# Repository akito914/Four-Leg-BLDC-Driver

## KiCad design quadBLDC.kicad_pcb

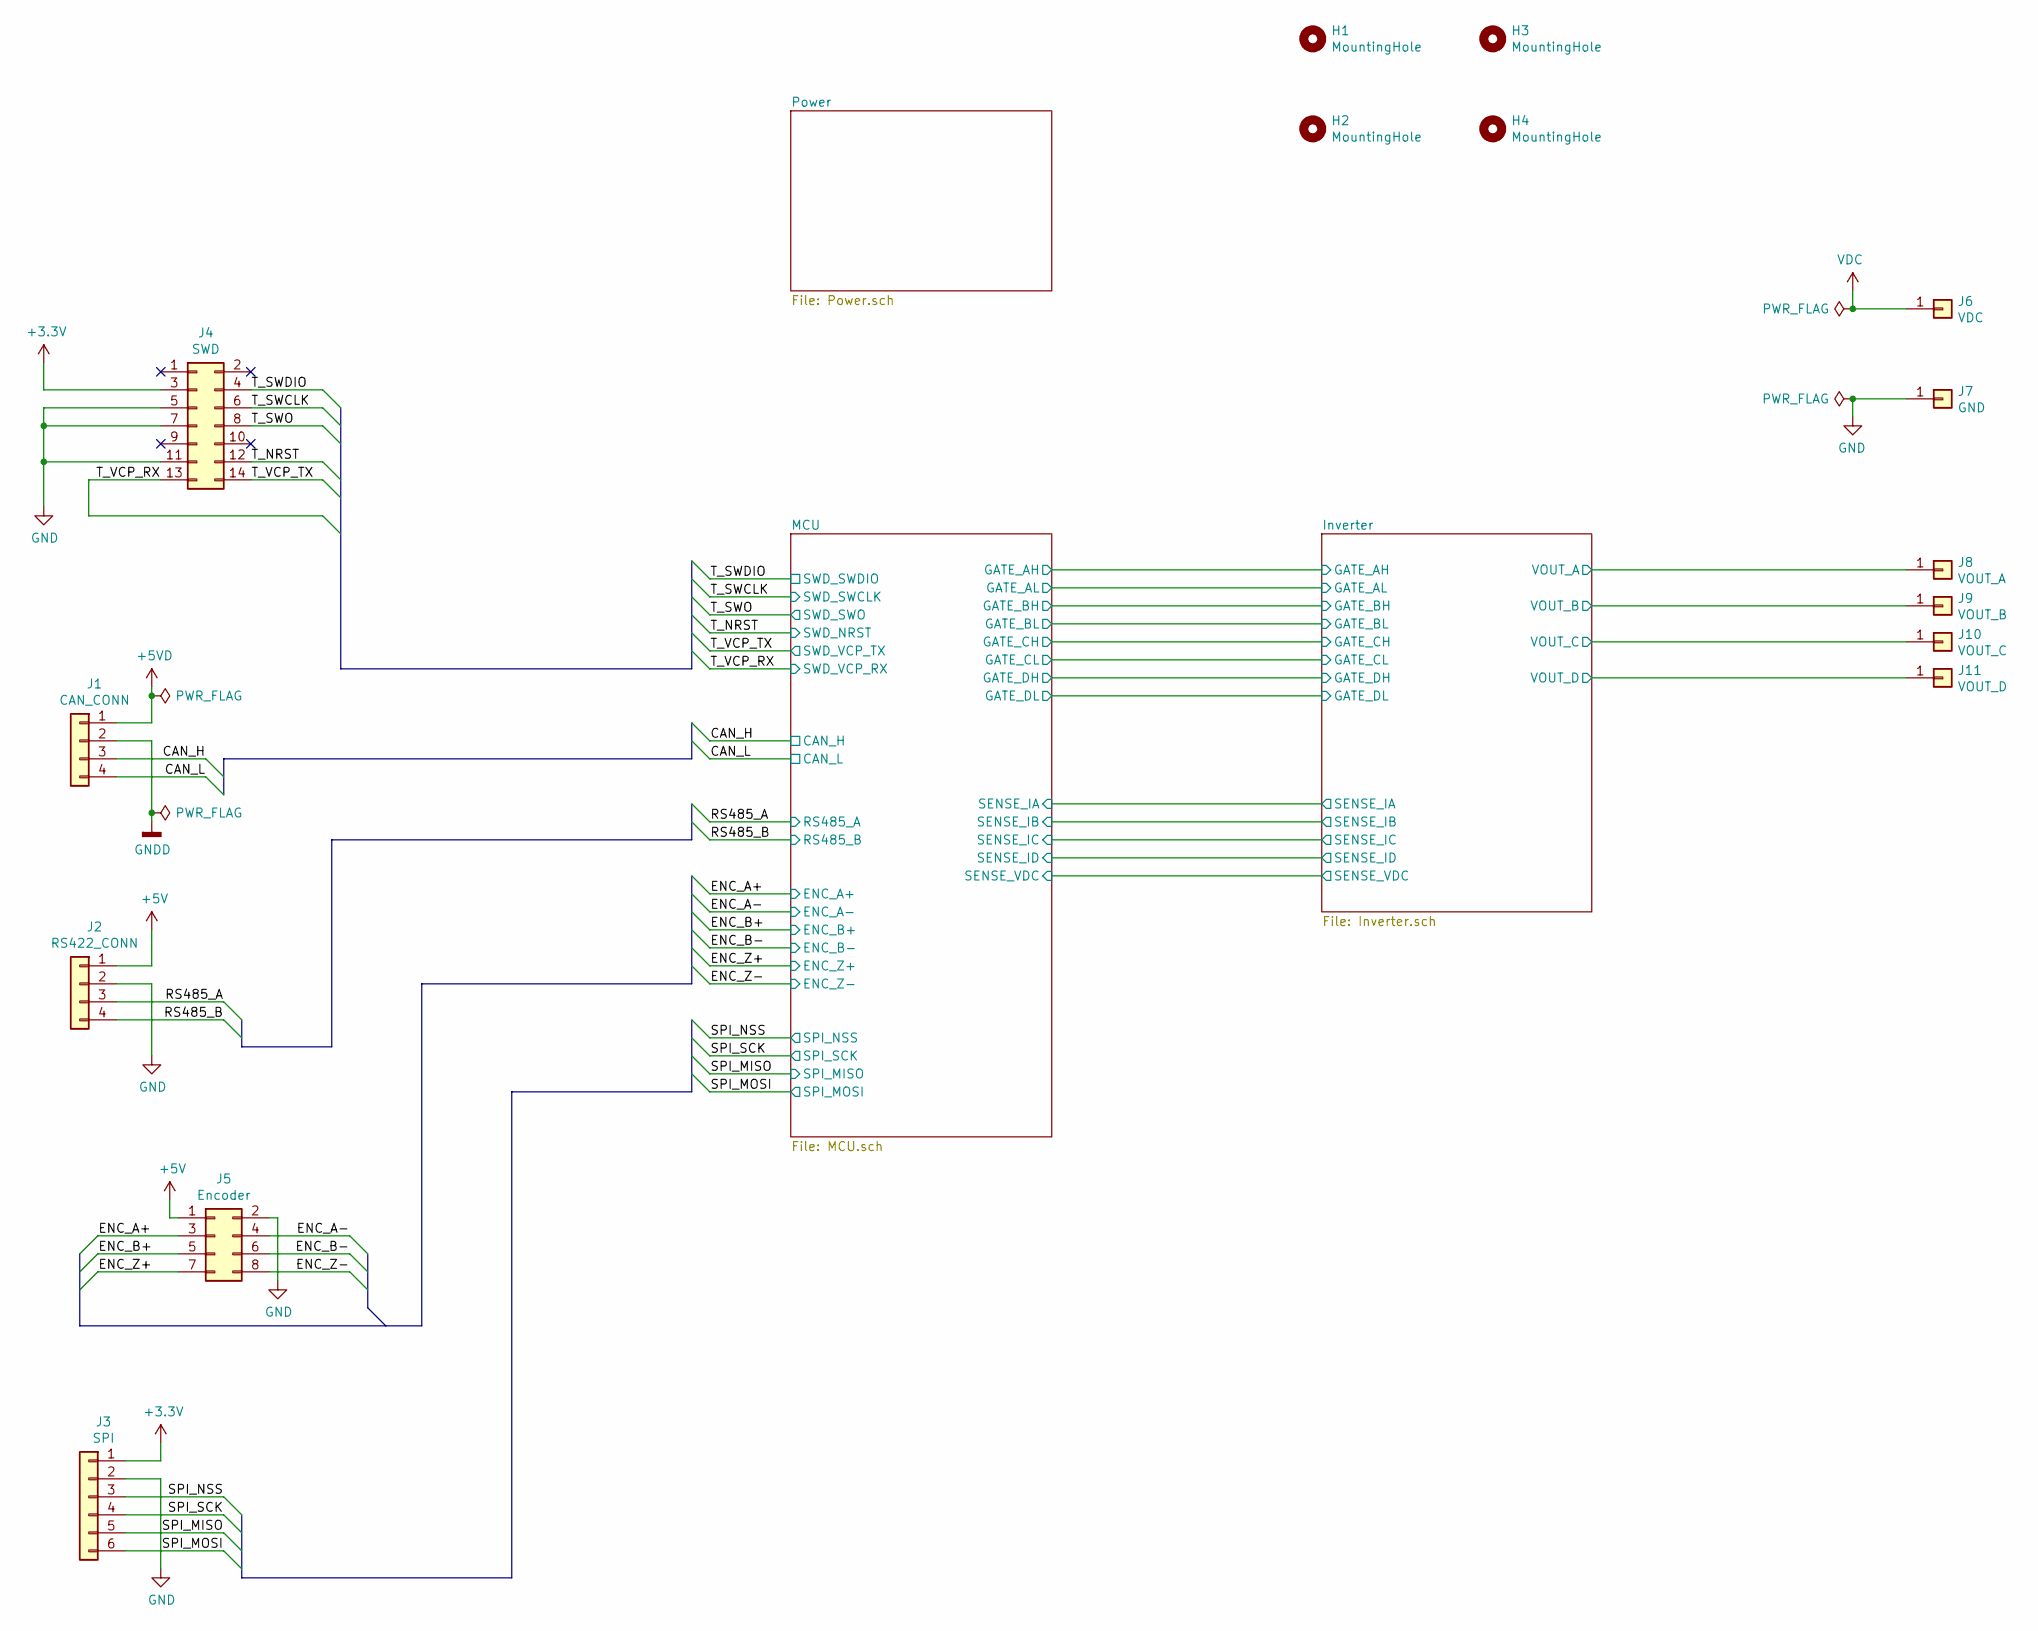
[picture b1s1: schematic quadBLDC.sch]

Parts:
H1, H2, H3, H4: MountingHole; MountingHole_3.2mm_M3
J1: CAN_CONN; JST_PH_B4B-PH-K_1x04_P2.00mm_Vertical
J2: RS422_CONN; JST_PH_B4B-PH-K_1x04_P2.00mm_Vertical
J3: SPI; JST_PH_B6B-PH-K_1x06_P2.00mm_Vertical
J4: SWD; PinHeader_2x07_P1.27mm_Vertical_SMD
J5: Encoder; JST_PHD_B8B-PHDSS_2x04_P2.00mm_Vertical
J6: VDC; SolderWire-2.5sqmm_1x01_D2.4mm_OD3.6mm
J7: GND; SolderWire-2.5sqmm_1x01_D2.4mm_OD3.6mm
J8: VOUT_A; SolderWire-2.5sqmm_1x01_D2.4mm_OD3.6mm
J9: VOUT_B; SolderWire-2.5sqmm_1x01_D2.4mm_OD3.6mm
J10: VOUT_C; SolderWire-2.5sqmm_1x01_D2.4mm_OD3.6mm
J11: VOUT_D; SolderWire-2.5sqmm_1x01_D2.4mm_OD3.6mm

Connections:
+3V3: J3.1, J4.3; also elsewhere on the board
+5V: J2.1, J5.1; also elsewhere on the board
+5VD: J1.1; also elsewhere on the board
/CAN_H: J1.3; also elsewhere on the board
/CAN_L: J1.4; also elsewhere on the board
/ENC_A+: J5.3; also elsewhere on the board
/ENC_A-: J5.4; also elsewhere on the board
/ENC_B+: J5.5; also elsewhere on the board
/ENC_B-: J5.6; also elsewhere on the board
/ENC_Z+: J5.7; also elsewhere on the board
/ENC_Z-: J5.8; also elsewhere on the board
/Inverter/VOUT_A: J8.1; also elsewhere on the board
/Inverter/VOUT_B: J9.1; also elsewhere on the board
/Inverter/VOUT_C: J10.1; also elsewhere on the board
/Inverter/VOUT_D: J11.1; also elsewhere on the board
/RS485_A: J2.3; also elsewhere on the board
/RS485_B: J2.4; also elsewhere on the board
/SPI_MISO: J3.5; also elsewhere on the board
/SPI_MOSI: J3.6; also elsewhere on the board
/SPI_NSS: J3.3; also elsewhere on the board
/SPI_SCK: J3.4; also elsewhere on the board
/T_NRST: J4.12; also elsewhere on the board
/T_SWCLK: J4.6; also elsewhere on the board
/T_SWDIO: J4.4; also elsewhere on the board
/T_SWO: J4.8; also elsewhere on the board
/T_VCP_RX: J4.13; also elsewhere on the board
/T_VCP_TX: J4.14; also elsewhere on the board
GND: J2.2, J3.2, J4.5, J4.7, J4.11, J5.2, J7.1; also elsewhere on the board
GNDD: J1.2; also elsewhere on the board
VDC: J6.1; also elsewhere on the board

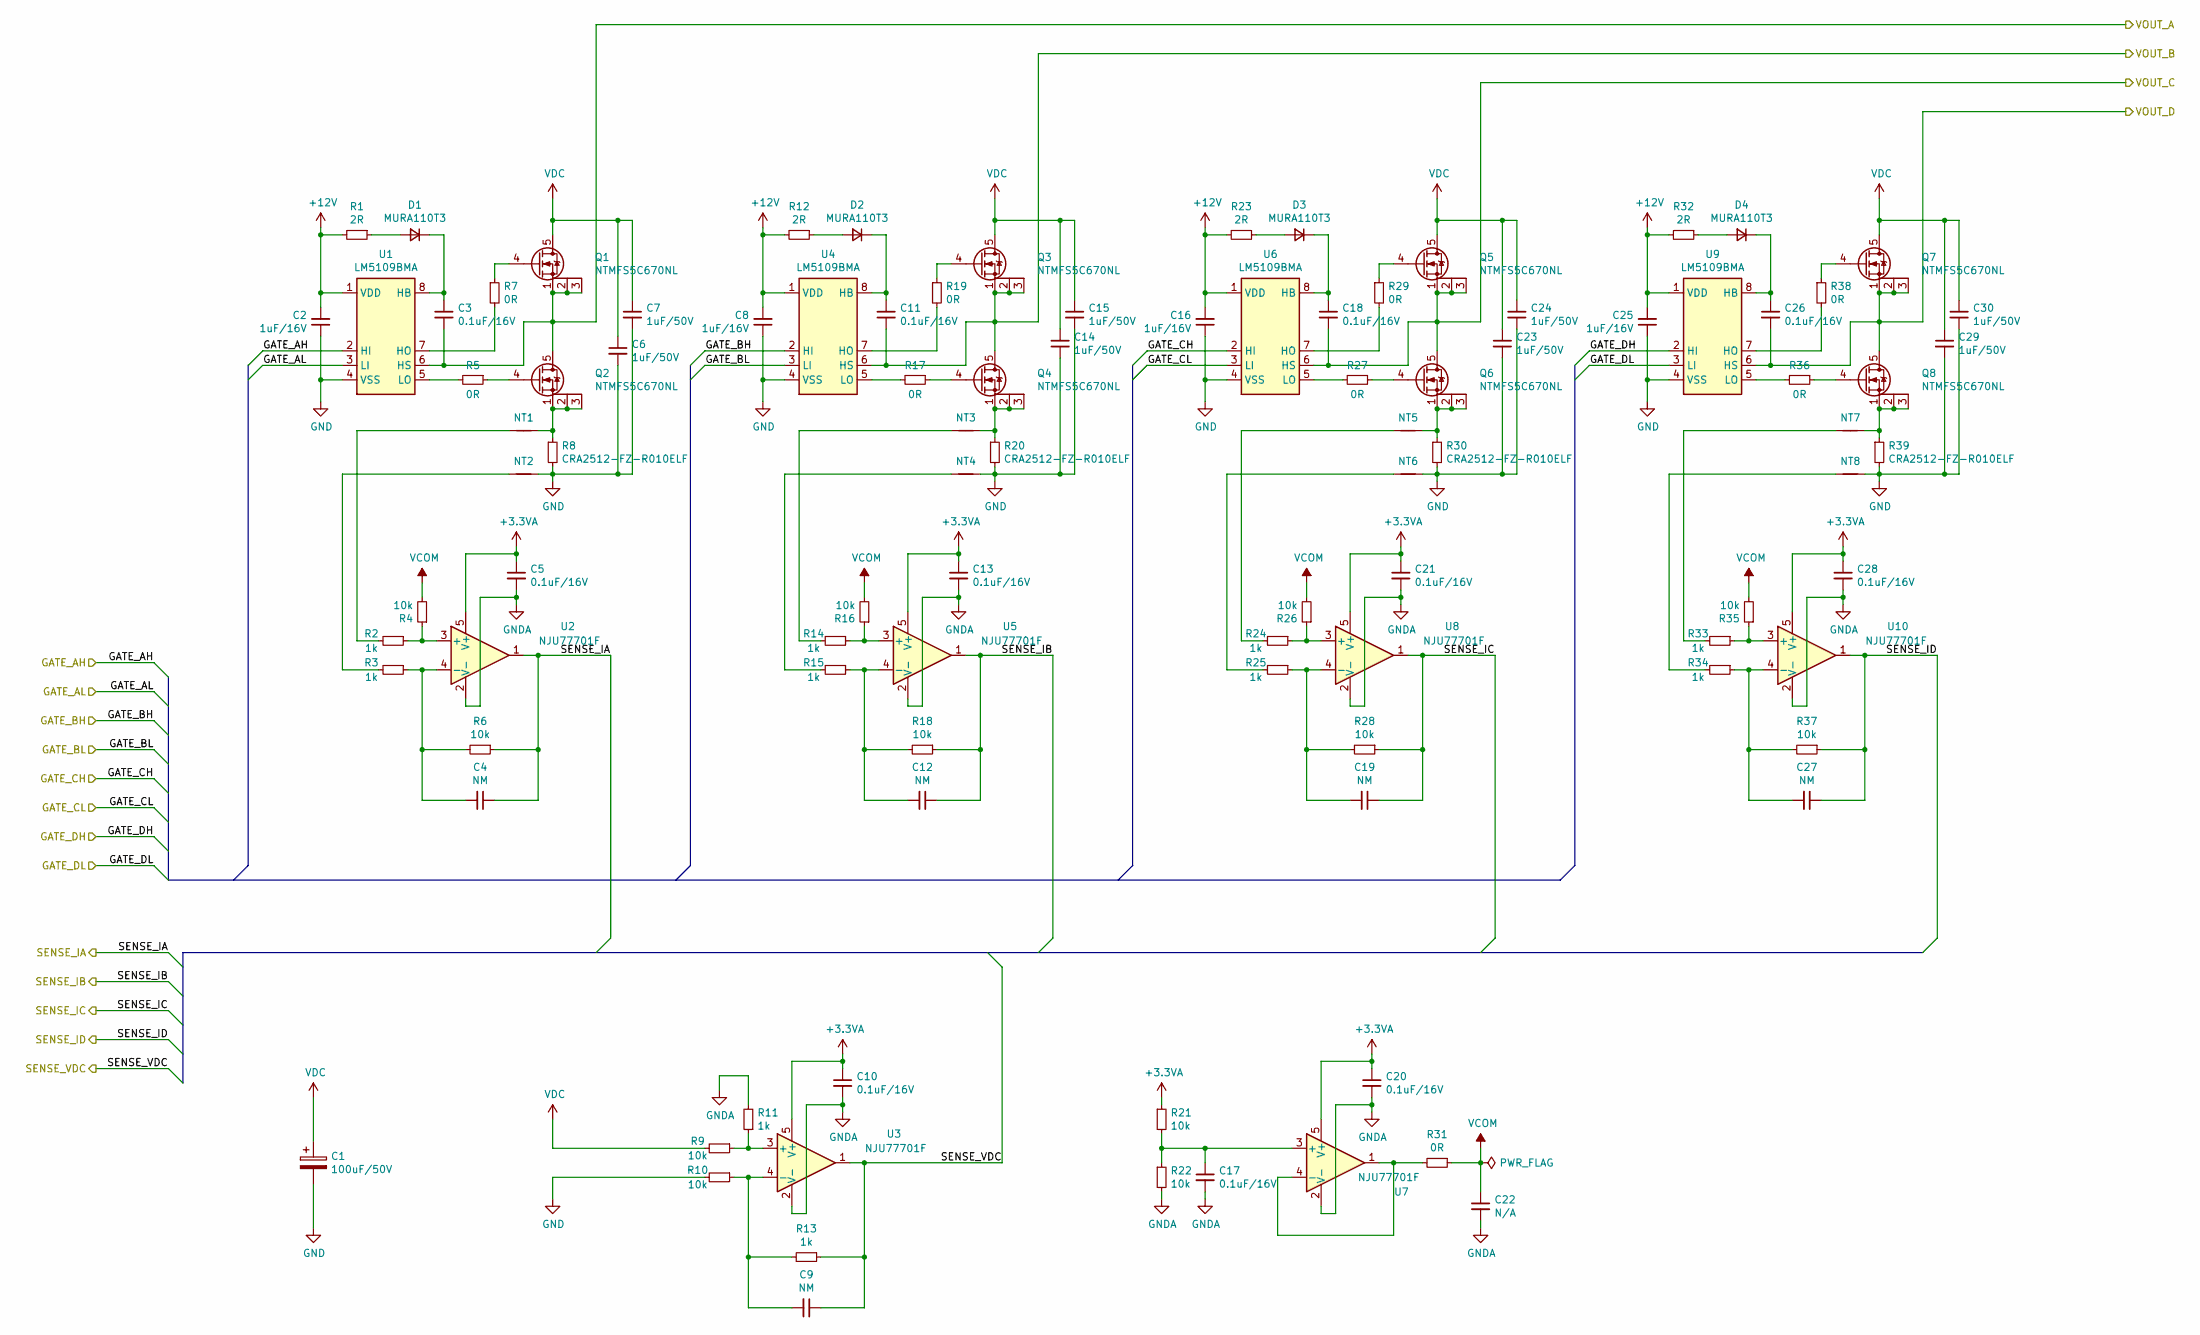
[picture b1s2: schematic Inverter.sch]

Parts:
C1: 100uF/50V; CP_Elec_10x10
C2, C8, C16, C25: 1uF/16V; C_0603_1608Metric
C3, C5, C10, C11, C13, C17, C18, C20, C21, C26, C28: 0.1uF/16V; C_0603_1608Metric
C4, C9, C12, C19, C27: NM; C_0603_1608Metric
C6, C7, C14, C15, C23, C24, C29, C30: 1uF/50V; C_0805_2012Metric
C22: N/A; C_0603_1608Metric
D1, D2, D3, D4: MURA110T3; D_SMA
NT1, NT2, NT3, NT4, NT5, NT6, NT7, NT8: Net-Tie_2; NetTie-2_SMD_Pad0.5mm
Q1, Q2, Q3, Q4, Q5, Q6, Q7, Q8: NTMFS5C670NL; PowerPAK_SO-8_Single
R1, R12, R23, R32: 2R; R_0603_1608Metric
R2, R3, R11, R13, R14, R15, R24, R25, R33, R34: 1k; R_0603_1608Metric
R4, R6, R9, R10, R16, R18, R21, R22, R26, R28, R35, R37: 10k; R_0603_1608Metric
R5, R7, R17, R19, R27, R29, R31, R36, R38: 0R; R_0603_1608Metric
R8, R20, R30, R39: CRA2512-FZ-R010ELF; R_2512_6332Metric
U1, U4, U6, U9: LM5109BMA; SOIC-8_3.9x4.9mm_P1.27mm
U2, U3, U5, U7, U8, U10: NJU77701F; SOT-23-5

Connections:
+3.3VA: C5.1, C10.1, C13.1, C20.1, C21.1, C28.1, R21.1, U2.5 (V+), U3.5 (V+), U5.5 (V+), U7.5 (V+), U8.5 (V+), U10.5 (V+); also elsewhere on the board
+12V: C2.2, C8.2, C16.2, C25.2, R1.2, R12.2, R23.2, R32.2, U1.1 (VDD), U4.1 (VDD), U6.1 (VDD), U9.1 (VDD); also elsewhere on the board
/Inverter/GATE_AH: U1.2 (HI); also elsewhere on the board
/Inverter/GATE_AL: U1.3 (LI); also elsewhere on the board
/Inverter/GATE_BH: U4.2 (HI); also elsewhere on the board
/Inverter/GATE_BL: U4.3 (LI); also elsewhere on the board
/Inverter/GATE_CH: U6.2 (HI); also elsewhere on the board
/Inverter/GATE_CL: U6.3 (LI); also elsewhere on the board
/Inverter/GATE_DH: U9.2 (HI); also elsewhere on the board
/Inverter/GATE_DL: U9.3 (LI); also elsewhere on the board
/Inverter/SENSE_IA: C4.1, R6.1, U2.1; also elsewhere on the board
/Inverter/SENSE_IB: C12.1, R18.1, U5.1; also elsewhere on the board
/Inverter/SENSE_IC: C19.1, R28.1, U8.1; also elsewhere on the board
/Inverter/SENSE_ID: C27.1, R37.1, U10.1; also elsewhere on the board
/Inverter/SENSE_VDC: C9.1, R13.1, U3.1; also elsewhere on the board
/Inverter/VOUT_A: C3.2, Q1.1 (S), Q1.2 (D), Q1.3 (D), Q2.5 (D), U1.6 (HS); also elsewhere on the board
/Inverter/VOUT_B: C11.2, Q3.1 (S), Q3.2 (D), Q3.3 (D), Q4.5 (D), U4.6 (HS); also elsewhere on the board
/Inverter/VOUT_C: C18.2, Q5.1 (S), Q5.2 (D), Q5.3 (D), Q6.5 (D), U6.6 (HS); also elsewhere on the board
/Inverter/VOUT_D: C26.2, Q7.1 (S), Q7.2 (D), Q7.3 (D), Q8.5 (D), U9.6 (HS); also elsewhere on the board
GND: C1.2, C2.1, C6.2, C7.2, C8.1, C14.2, C15.2, C16.1, C23.2, C24.2, C25.1, C29.2, C30.2, NT2.1, NT4.1, NT6.1, NT8.1, R8.2, R10.2, R20.2, R30.2, R39.2, U1.4 (VSS), U4.4 (VSS), U6.4 (VSS), U9.4 (VSS); also elsewhere on the board
GNDA: C5.2, C10.2, C13.2, C17.2, C20.2, C21.2, C22.2, C28.2, R11.2, R22.2, U2.2 (V-), U3.2 (V-), U5.2 (V-), U7.2 (V-), U8.2 (V-), U10.2 (V-); also elsewhere on the board
unnamed: C3.1, D1.1 (K), U1.8 (HB)
unnamed: C4.2, R3.1, R6.2, U2.4 (-)
unnamed: C9.2, R10.1, R13.2, U3.4 (-)
unnamed: C11.1, D2.1 (K), U4.8 (HB)
unnamed: C12.2, R15.1, R18.2, U5.4 (-)
unnamed: C17.1, R21.2, R22.1, U7.3 (+)
unnamed: C18.1, D3.1 (K), U6.8 (HB)
unnamed: C19.2, R25.1, R28.2, U8.4 (-)
unnamed: C26.1, D4.1 (K), U9.8 (HB)
unnamed: C27.2, R34.1, R37.2, U10.4 (-)
unnamed: D1.2 (A), R1.1
unnamed: D2.2 (A), R12.1
unnamed: D3.2 (A), R23.1
unnamed: D4.2 (A), R32.1
unnamed: NT1.1, Q2.1 (S), Q2.2 (D), Q2.3 (D), R8.1
unnamed: NT1.2, R2.2
unnamed: NT2.2, R3.2
unnamed: NT3.1, Q4.1 (S), Q4.2 (D), Q4.3 (D), R20.1
unnamed: NT3.2, R14.2
unnamed: NT4.2, R15.2
unnamed: NT5.1, Q6.1 (S), Q6.2 (D), Q6.3 (D), R30.1
unnamed: NT5.2, R24.2
unnamed: NT6.2, R25.2
unnamed: NT7.1, Q8.1 (S), Q8.2 (D), Q8.3 (D), R39.1
unnamed: NT7.2, R33.2
unnamed: NT8.2, R34.2
unnamed: Q1.4 (G), R7.1
unnamed: Q2.4 (G), R5.1
unnamed: Q3.4 (G), R19.1
unnamed: Q4.4 (G), R17.1
unnamed: Q5.4 (G), R29.1
unnamed: Q6.4 (G), R27.1
unnamed: Q7.4 (G), R38.1
unnamed: Q8.4 (G), R36.1
unnamed: R2.1, R4.1, U2.3 (+)
unnamed: R5.2, U1.5 (LO)
unnamed: R7.2, U1.7 (HO)
unnamed: R9.1, R11.1, U3.3 (+)
unnamed: R14.1, R16.1, U5.3 (+)
unnamed: R17.2, U4.5 (LO)
unnamed: R19.2, U4.7 (HO)
unnamed: R24.1, R26.1, U8.3 (+)
unnamed: R27.2, U6.5 (LO)
unnamed: R29.2, U6.7 (HO)
unnamed: R31.2, U7.1, U7.4 (-)
unnamed: R33.1, R35.1, U10.3 (+)
unnamed: R36.2, U9.5 (LO)
unnamed: R38.2, U9.7 (HO)
VCOM: C22.1, R4.2, R16.2, R26.2, R31.1, R35.2
VDC: C1.1, C6.1, C7.1, C14.1, C15.1, C23.1, C24.1, C29.1, C30.1, Q1.5 (D), Q3.5 (D), Q5.5 (D), Q7.5 (D), R9.2; also elsewhere on the board

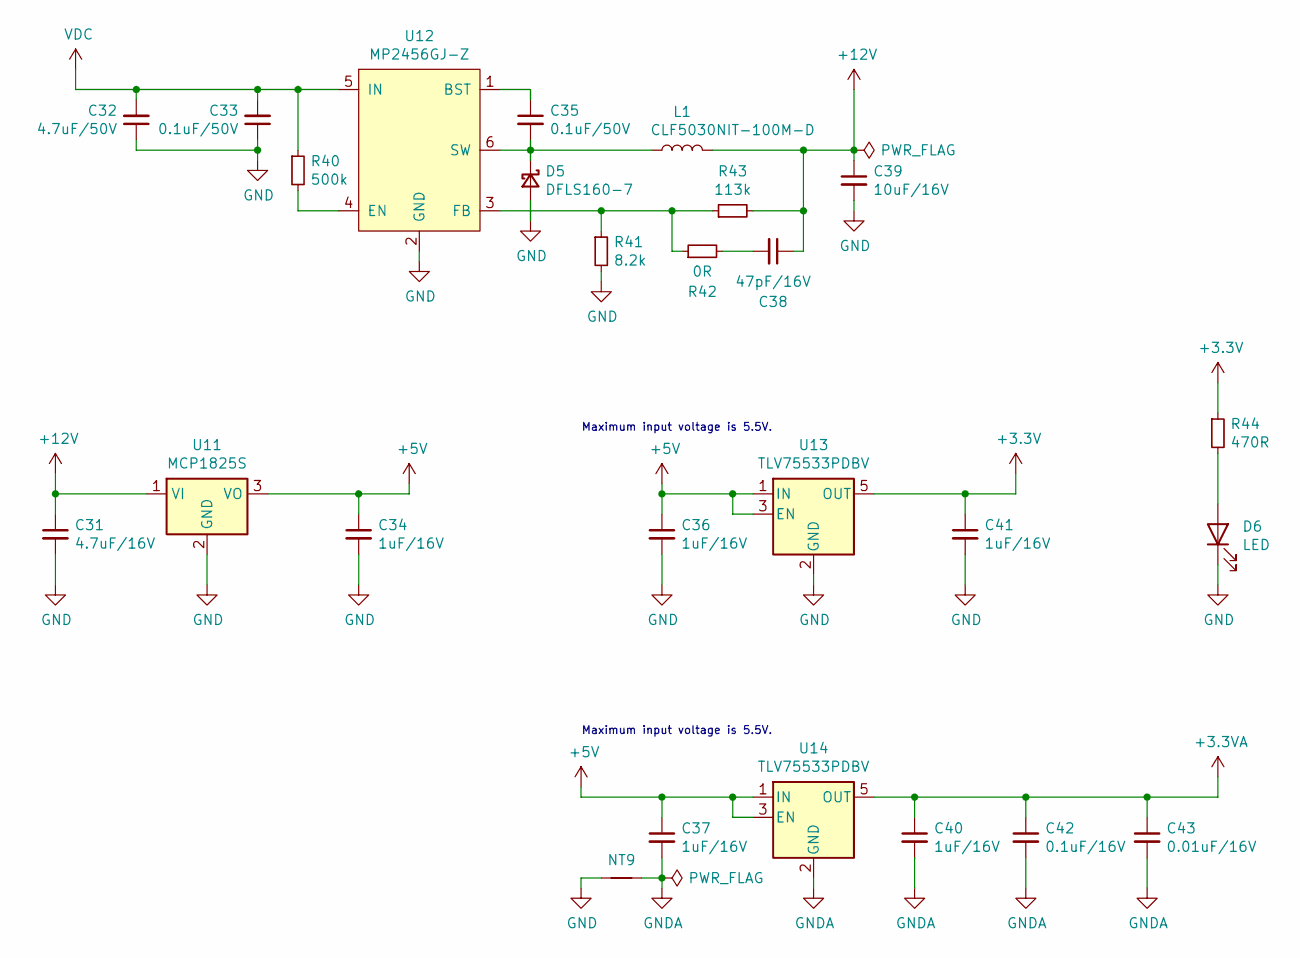
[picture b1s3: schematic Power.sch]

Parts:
C31: 4.7uF/16V; C_0805_2012Metric
C32: 4.7uF/50V; C_0805_2012Metric
C33, C35: 0.1uF/50V; C_0603_1608Metric
C34, C36, C37, C40, C41: 1uF/16V; C_0603_1608Metric
C38: 47pF/16V; C_0603_1608Metric
C39: 10uF/16V; C_0805_2012Metric
C42: 0.1uF/16V; C_0603_1608Metric
C43: 0.01uF/16V; C_0603_1608Metric
D5: DFLS160-7; D_PowerDI-123
D6: LED; LED_0603_1608Metric
L1: CLF5030NIT-100M-D; L_TDK_CLF5030NI-D
NT9: Net-Tie_2; NetTie-2_SMD_Pad0.5mm
R40: 500k; R_0603_1608Metric
R41: 8.2k; R_0603_1608Metric
R42: 0R; R_0603_1608Metric
R43: 113k; R_0603_1608Metric
R44: 470R; R_0603_1608Metric
U11: MCP1825S; SOT-223-3_TabPin2
U12: MP2456GJ-Z; SOT-23-6
U13, U14: TLV75533PDBV; SOT-23-5

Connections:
+3.3VA: C40.1, C42.1, C43.1, U14.5 (OUT); also elsewhere on the board
+3V3: C41.1, R44.1, U13.5 (OUT); also elsewhere on the board
+5V: C34.1, C36.1, C37.1, U11.3 (VO), U13.1 (IN), U13.3 (EN), U14.1 (IN), U14.3 (EN); also elsewhere on the board
+12V: C31.1, C38.1, C39.1, L1.2, R43.2, U11.1 (VI); also elsewhere on the board
GND: C31.2, C32.1, C33.1, C34.2, C36.2, C39.2, C41.2, D5.2 (A), D6.1 (K), NT9.2, R41.2, U11.2 (GND), U12.2 (GND), U13.2 (GND); also elsewhere on the board
GNDA: C37.2, C40.2, C42.2, C43.2, NT9.1, U14.2 (GND); also elsewhere on the board
unnamed: C35.1, U12.1 (BST)
unnamed: C35.2, D5.1 (K), L1.1, U12.6 (SW)
unnamed: C38.2, R42.2
unnamed: D6.2 (A), R44.2
unnamed: R40.2, U12.4 (EN)
unnamed: R41.1, R42.1, R43.1, U12.3 (FB)
VDC: C32.2, C33.2, R40.1, U12.5 (IN); also elsewhere on the board

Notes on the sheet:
Maximum input voltage is 5.5V.

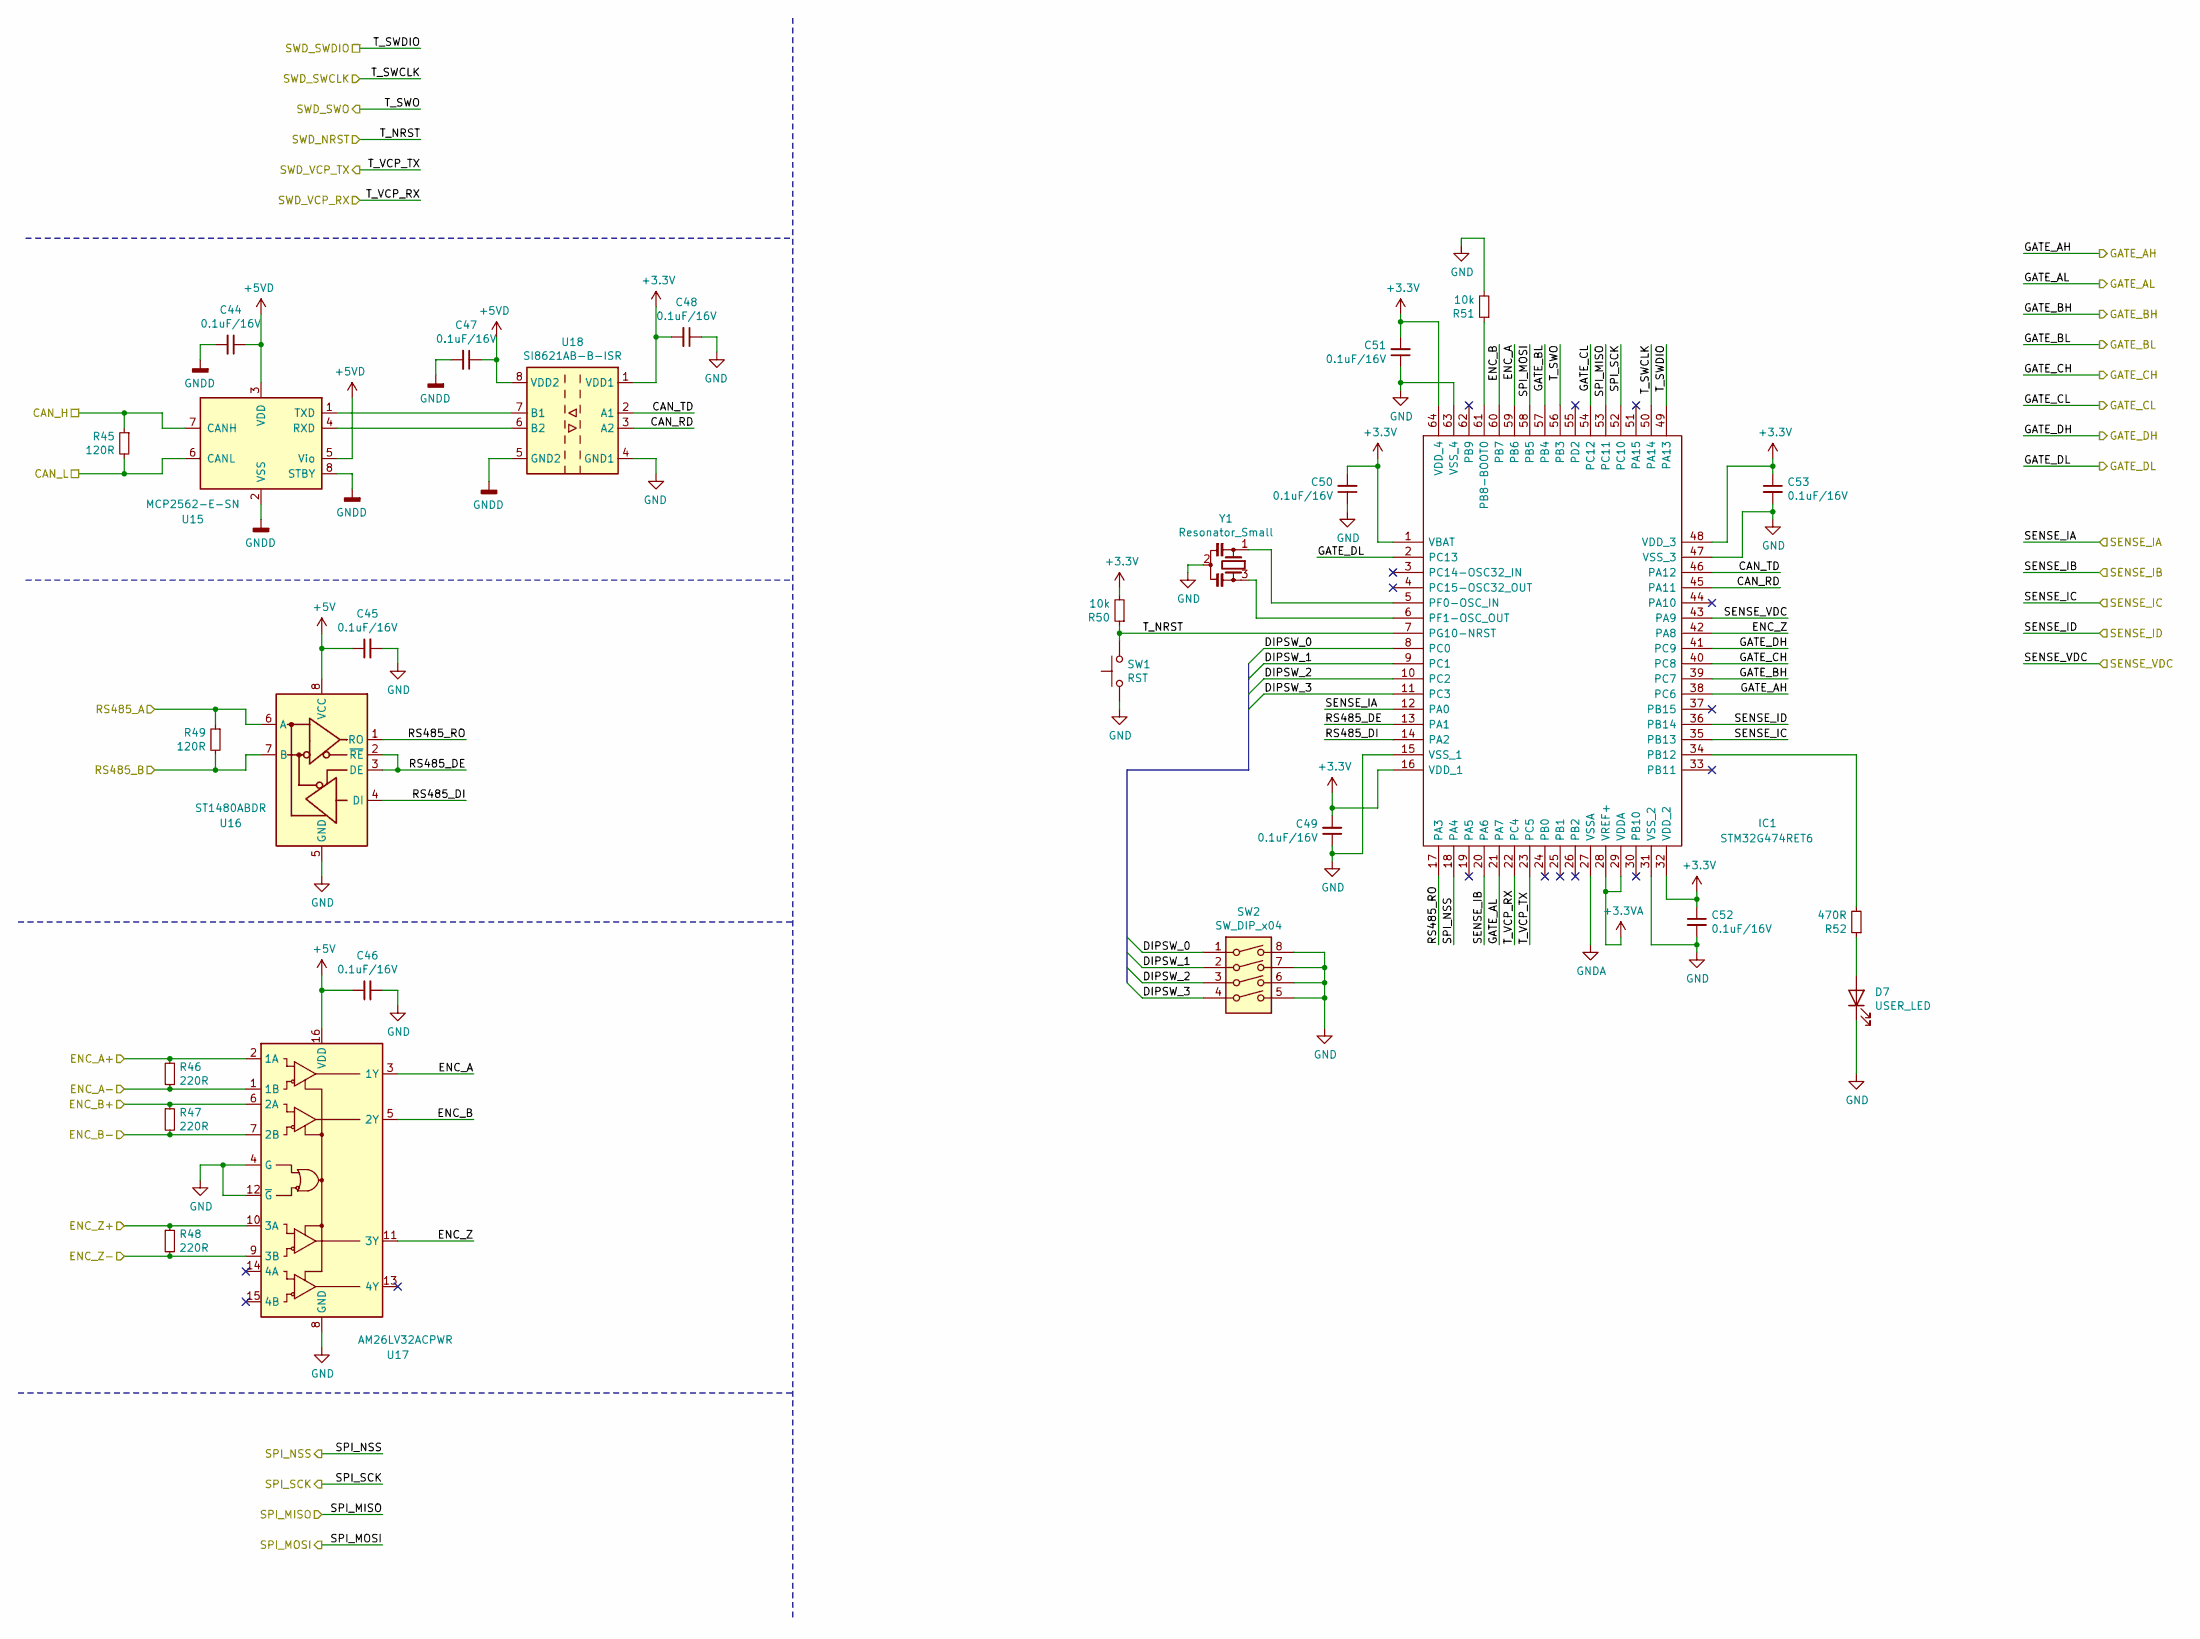
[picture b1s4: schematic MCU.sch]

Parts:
C44, C45, C46, C47, C48, C49, C50, C51, C52, C53: 0.1uF/16V; C_0603_1608Metric
D7: USER_LED; LED_0603_1608Metric
IC1: STM32G474RET6; QFP50P1200X1200X160-64N
R45, R49: 120R; R_0603_1608Metric
R46, R47, R48: 220R; R_0603_1608Metric
R50, R51: 10k; R_0603_1608Metric
R52: 470R; R_0603_1608Metric
SW1: RST; SKRPACE010
SW2: SW_DIP_x04; SOIC127P812X230-8N
U15: MCP2562-E-SN; SOIC-8_3.9x4.9mm_P1.27mm
U16: ST1480ABDR; SOIC-8_3.9x4.9mm_P1.27mm
U17: AM26LV32ACPWR; TSSOP-16_4.4x5mm_P0.65mm
U18: SI8621AB-B-ISR; SOIC-8_3.9x4.9mm_P1.27mm
Y1: Resonator_Small; Resonator_SMD_muRata_CSTxExxV-3Pin_3.0x1.1mm

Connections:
+3.3VA: IC1.28 (VREF+), IC1.29 (VDDA); also elsewhere on the board
+3V3: C48.2, C49.2, C50.2, C51.2, C52.1, C53.1, IC1.1 (VBAT), IC1.16 (VDD_1), IC1.32 (VDD_2), IC1.48 (VDD_3), IC1.64 (VDD_4), R50.2, U18.1 (VDD1); also elsewhere on the board
+5V: C45.1, C46.1, U16.8 (VCC), U17.16 (VDD); also elsewhere on the board
+5VD: C44.1, C47.1, U15.3 (VDD), U15.5 (Vio), U18.8 (VDD2); also elsewhere on the board
/CAN_H: R45.1, U15.7 (CANH); also elsewhere on the board
/CAN_L: R45.2, U15.6 (CANL); also elsewhere on the board
/ENC_A+: R46.1, U17.2 (1A); also elsewhere on the board
/ENC_A-: R46.2, U17.1 (1B); also elsewhere on the board
/ENC_B+: R47.1, U17.6 (2A); also elsewhere on the board
/ENC_B-: R47.2, U17.7 (2B); also elsewhere on the board
/ENC_Z+: R48.1, U17.10 (3A); also elsewhere on the board
/ENC_Z-: R48.2, U17.9 (3B); also elsewhere on the board
/Inverter/GATE_AH: IC1.38 (PC6); also elsewhere on the board
/Inverter/GATE_AL: IC1.21 (PA7); also elsewhere on the board
/Inverter/GATE_BH: IC1.39 (PC7); also elsewhere on the board
/Inverter/GATE_BL: IC1.57 (PB4); also elsewhere on the board
/Inverter/GATE_CH: IC1.40 (PC8); also elsewhere on the board
/Inverter/GATE_CL: IC1.54 (PC12); also elsewhere on the board
/Inverter/GATE_DH: IC1.41 (PC9); also elsewhere on the board
/Inverter/GATE_DL: IC1.2 (PC13); also elsewhere on the board
/Inverter/SENSE_IA: IC1.12 (PA0); also elsewhere on the board
/Inverter/SENSE_IB: IC1.20 (PA6); also elsewhere on the board
/Inverter/SENSE_IC: IC1.35 (PB13); also elsewhere on the board
/Inverter/SENSE_ID: IC1.36 (PB14); also elsewhere on the board
/Inverter/SENSE_VDC: IC1.43 (PA9); also elsewhere on the board
/MCU/CAN_RD: IC1.45 (PA11), U18.3 (A2)
/MCU/CAN_TD: IC1.46 (PA12), U18.2 (A1)
/MCU/DIPSW_0: IC1.8 (PC0), SW2.1
/MCU/DIPSW_1: IC1.9 (PC1), SW2.2
/MCU/DIPSW_2: IC1.10 (PC2), SW2.3
/MCU/DIPSW_3: IC1.11 (PC3), SW2.4
/MCU/ENC_A: IC1.59 (PB6), U17.3 (1Y)
/MCU/ENC_B: IC1.60 (PB7), U17.5 (2Y)
/MCU/ENC_Z: IC1.42 (PA8), U17.11 (3Y)
/MCU/RS485_DE: IC1.13 (PA1), U16.2 (~RE), U16.3 (DE)
/MCU/RS485_DI: IC1.14 (PA2), U16.4 (DI)
/MCU/RS485_RO: IC1.17 (PA3), U16.1 (RO)
/RS485_A: R49.1, U16.6 (A); also elsewhere on the board
/RS485_B: R49.2, U16.7 (B); also elsewhere on the board
/SPI_MISO: IC1.53 (PC11); also elsewhere on the board
/SPI_MOSI: IC1.58 (PB5); also elsewhere on the board
/SPI_NSS: IC1.18 (PA4); also elsewhere on the board
/SPI_SCK: IC1.52 (PC10); also elsewhere on the board
/T_NRST: IC1.7 (PG10-NRST), R50.1, SW1.2; also elsewhere on the board
/T_SWCLK: IC1.50 (PA14); also elsewhere on the board
/T_SWDIO: IC1.49 (PA13); also elsewhere on the board
/T_SWO: IC1.56 (PB3); also elsewhere on the board
/T_VCP_RX: IC1.22 (PC4); also elsewhere on the board
/T_VCP_TX: IC1.23 (PC5); also elsewhere on the board
GND: C45.2, C46.2, C48.1, C49.1, C50.1, C51.1, C52.2, C53.2, D7.1 (K), IC1.15 (VSS_1), IC1.31 (VSS_2), IC1.47 (VSS_3), IC1.63 (VSS_4), R51.2, SW1.1, SW2.5, SW2.6, SW2.7, SW2.8, U16.5 (GND), U17.4 (G), U17.8 (GND), U17.12 (~G), U18.4 (GND1), Y1.2; also elsewhere on the board
GNDA: IC1.27 (VSSA); also elsewhere on the board
GNDD: C44.2, C47.2, U15.2 (VSS), U15.8 (STBY), U18.5 (GND2); also elsewhere on the board
unnamed: D7.2 (A), R52.1
unnamed: IC1.5 (PF0-OSC_IN), Y1.1
unnamed: IC1.6 (PF1-OSC_OUT), Y1.3
unnamed: IC1.34 (PB12), R52.2
unnamed: IC1.61 (PB8-BOOT0), R51.1
unnamed: U15.1 (TXD), U18.7 (B1)
unnamed: U15.4 (RXD), U18.6 (B2)

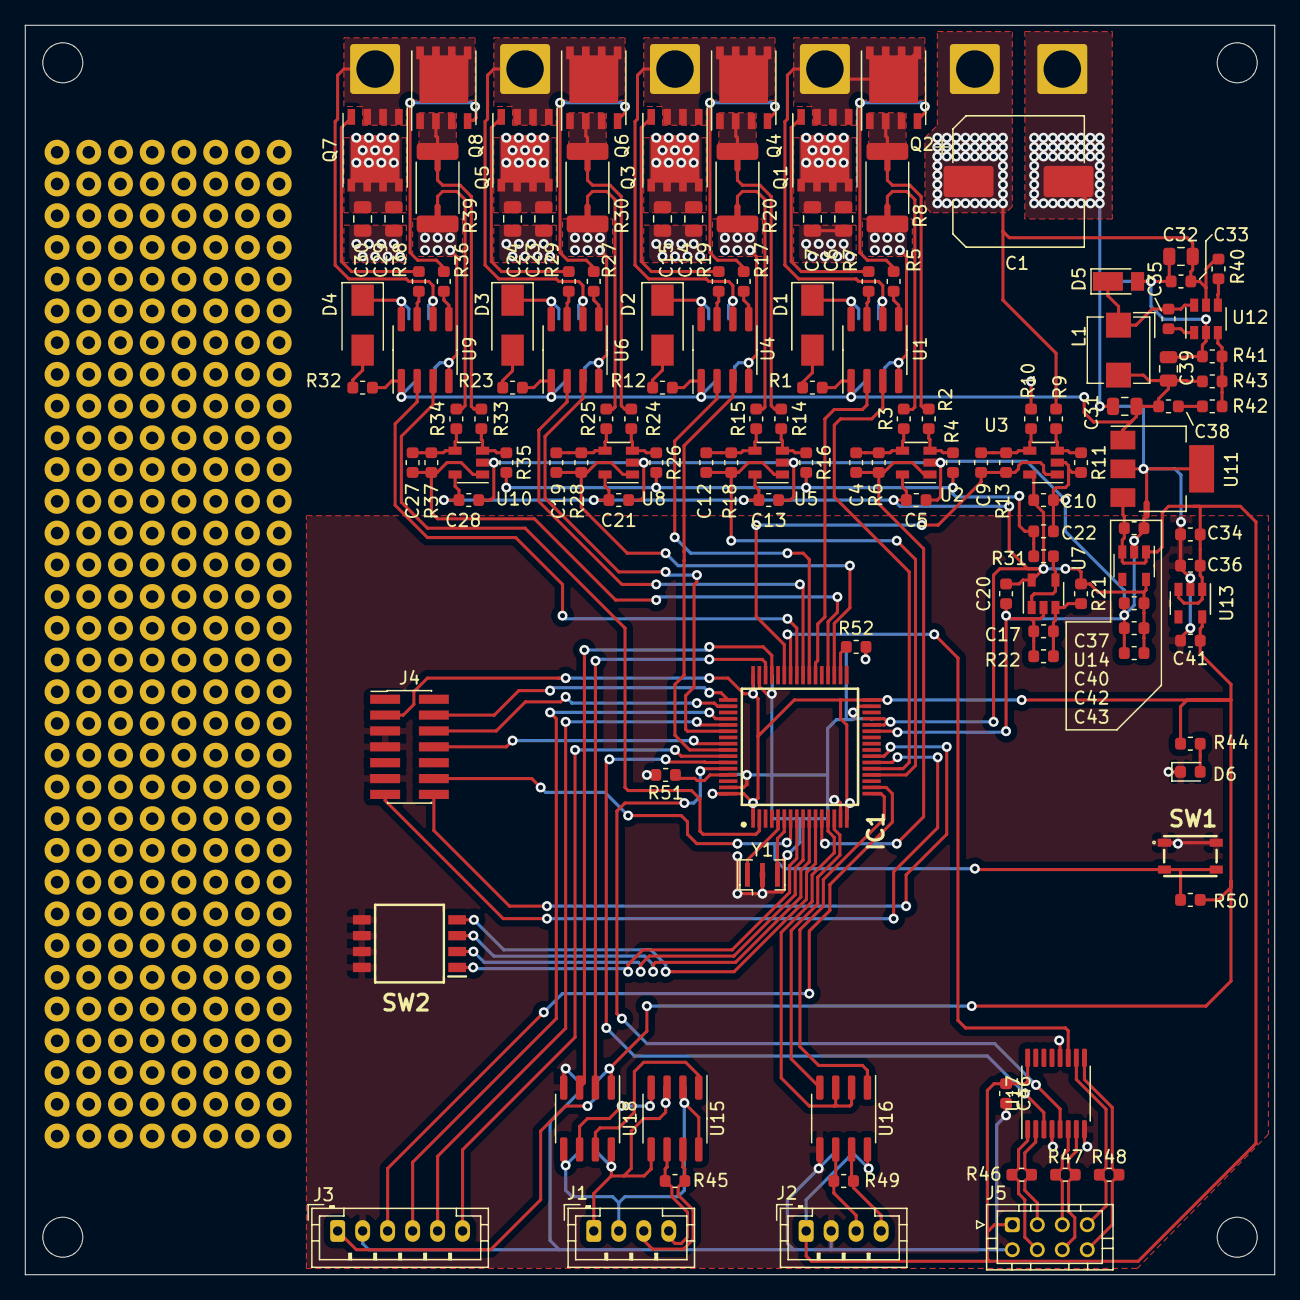
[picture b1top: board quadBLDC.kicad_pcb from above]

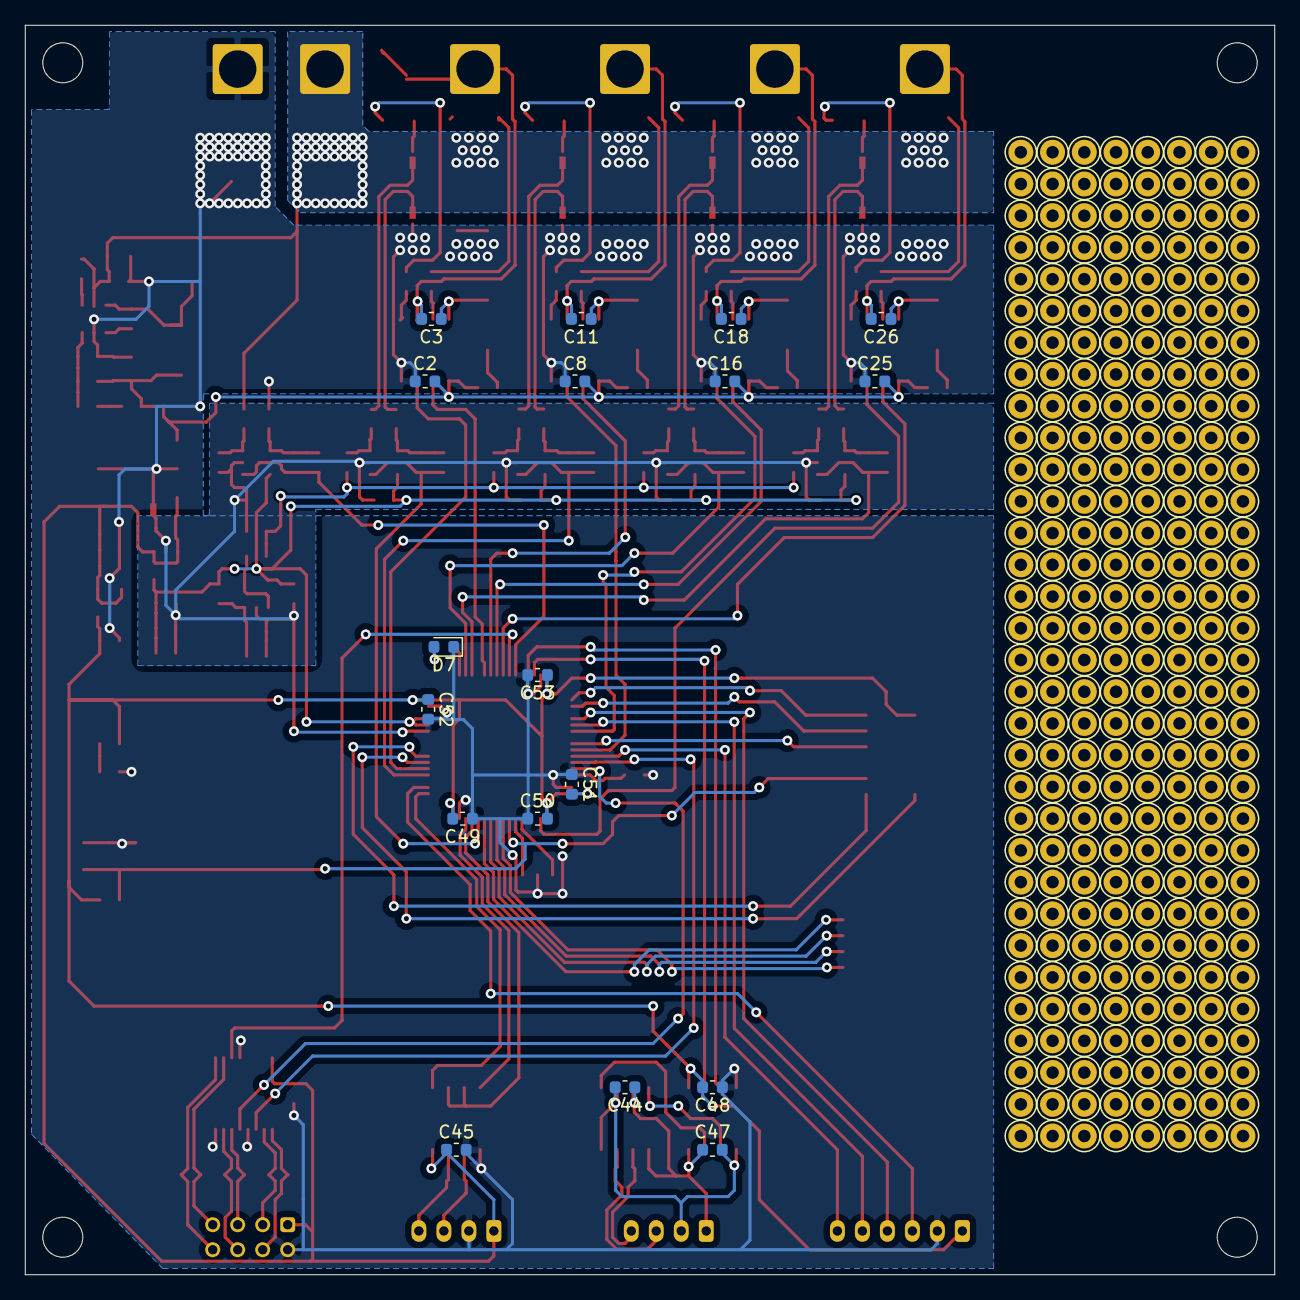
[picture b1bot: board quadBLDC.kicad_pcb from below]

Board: 2 copper layers, 100.0 x 100.0 mm, 167 parts (18 on the bottom side), 120 nets.

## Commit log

2021-02-25 first
2021-03-21 Update: 回路図完成
2021-03-21 wip: レグの配置途中
2021-03-22 Fix: ゲートドライブの配線修正
2021-03-22 Update: レグのデカップリングキャパシタ位置変更
2021-03-22 wip: レグ配置中
2021-03-24 wip: レグ配線中
2021-03-25 wip: 配置
2021-04-09 Update: 回路図、DCリンクCap1つ削除、アノテーションリセット
2021-04-09 Update: アナログリファレンスをLDOからに変更
2021-05-23 wip CAN STBYピン修正
2021-05-23 Update : 配線一段落
2022-09-09 Update: シルク配置
2022-10-01 Add: ガーバー書き出し
